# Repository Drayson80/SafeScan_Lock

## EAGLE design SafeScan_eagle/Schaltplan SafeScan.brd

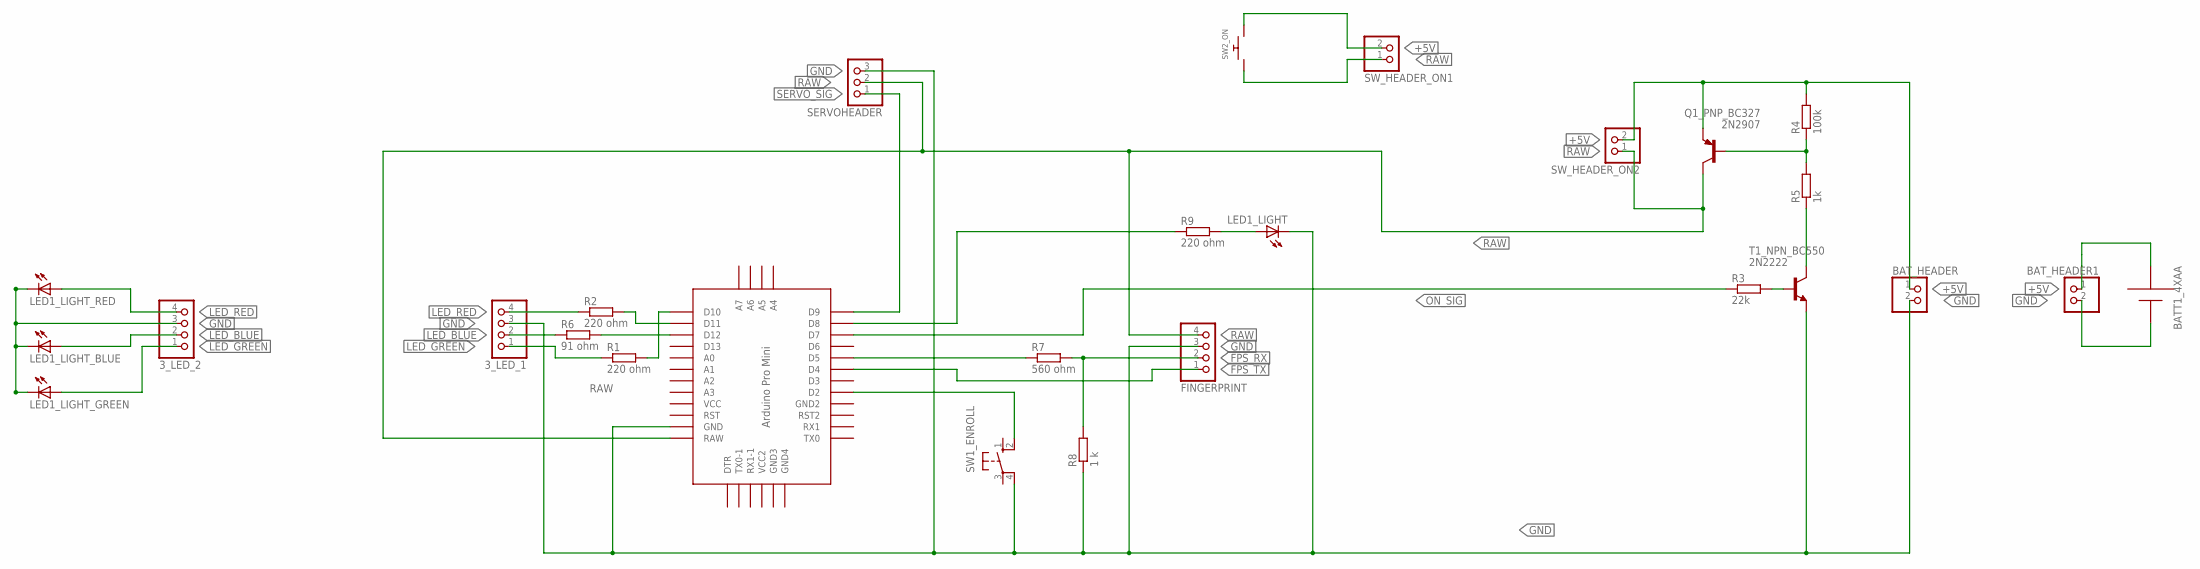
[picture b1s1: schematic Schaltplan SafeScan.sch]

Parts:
3_LED_1, 3_LED_2: PINHD-1X4; 1X04
ARDUINO_PRO_MINI_3.3: PRO-MINI
BATT1_4XAA: AAA; 12BH412
BAT_HEADER, BAT_HEADER1: PINHD-1X2; 1X02
FINGERPRINT: PINHD-1X4; 1X04
LED1_LIGHT, LED1_LIGHT_BLUE, LED1_LIGHT_GREEN, LED1_LIGHT_RED: LED5MM
Q1_PNP_BC327: 2N2907; TO92-EBC-OVAL
R1, R2, R9: 220 ohm; 0204/5
R3: 22k; 0204/5
R4: 100k; 0204/5
R5: 1k; 0204/5
R6: 91 ohm; 0204/5
R7: 560 ohm; 0207/15
R8: 1 k; 0204/5
SERVOHEADER: PINHD-1X3CB; 1X03-CLEANBIG
SW1_ENROLL: 10-XX; B3F-10XX
SW2_ON: SWITCH_PUSHBUTTONEVQ-PE; TACT_PANA-EVQ
SW_HEADER_ON1, SW_HEADER_ON2: PINHD-1X2; 1X02
T1_NPN_BC550: 2N2222; TO92-EBC-OVAL

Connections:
+5V: BATT1_4XAA.-, BAT_HEADER.1, BAT_HEADER1.1, Q1_PNP_BC327.E, R4.2, SW2_ON.P$2, SW_HEADER_ON1.2, SW_HEADER_ON2.2
FPS_RX: FINGERPRINT.2, R7.2, R8.2
FPS_TX: ARDUINO_PRO_MINI_3.3.D4, FINGERPRINT.1
GND: 3_LED_1.3, 3_LED_2.3, ARDUINO_PRO_MINI_3.3.GND, BATT1_4XAA.+, BAT_HEADER.2, BAT_HEADER1.2, FINGERPRINT.3, LED1_LIGHT.K (C), LED1_LIGHT_BLUE.K (C), LED1_LIGHT_GREEN.K (C), LED1_LIGHT_RED.K (C), R8.1, SERVOHEADER.3, SW1_ENROLL.4 (P1), T1_NPN_BC550.E
LED_BLUE: 3_LED_1.2, 3_LED_2.2, LED1_LIGHT_BLUE.A, R6.1
LED_GREEN: 3_LED_1.1, 3_LED_2.1, LED1_LIGHT_GREEN.A, R1.1
LED_RED: 3_LED_1.4, 3_LED_2.4, LED1_LIGHT_RED.A, R2.1
unnamed: ARDUINO_PRO_MINI_3.3.D5, R7.1
unnamed: R5.1, T1_NPN_BC550.C
unnamed: ARDUINO_PRO_MINI_3.3.D2, SW1_ENROLL.2 (S1)
unnamed: ARDUINO_PRO_MINI_3.3.D8, R9.1
unnamed: ARDUINO_PRO_MINI_3.3.D10, R1.2
unnamed: ARDUINO_PRO_MINI_3.3.D11, R2.2
unnamed: ARDUINO_PRO_MINI_3.3.D12, R6.2
unnamed: Q1_PNP_BC327.B, R4.1, R5.2
unnamed: LED1_LIGHT.A, R9.2
unnamed: R3.2, T1_NPN_BC550.B
ON_SIG: ARDUINO_PRO_MINI_3.3.D7, R3.1
RAW: ARDUINO_PRO_MINI_3.3.RAW, FINGERPRINT.4, Q1_PNP_BC327.C, SERVOHEADER.2, SW2_ON.P$1, SW_HEADER_ON1.1, SW_HEADER_ON2.1
SERVO_SIG: ARDUINO_PRO_MINI_3.3.D9, SERVOHEADER.1

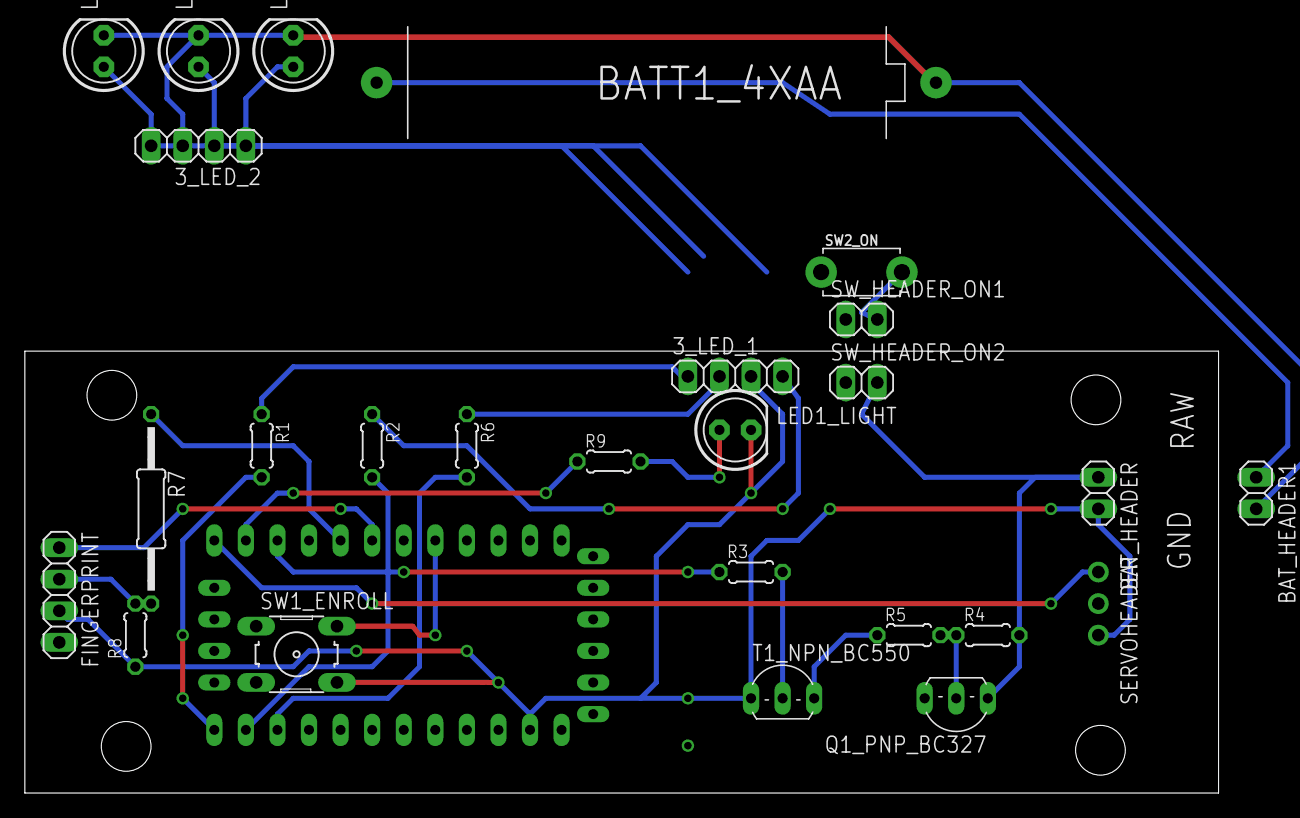
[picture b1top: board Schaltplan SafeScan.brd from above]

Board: 2 copper layers, 96.0 x 35.5 mm, 27 parts (0 on the bottom side), 20 nets.

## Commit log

2018-02-07 upload
    upload of status quo, first code iteration
2018-02-07 Improvements
    added self-holding power function, different power source, additional LED, restructured code...
2018-08-29 update infos
2018-09-06 Changes to make it work...
2018-09-07 rework...
2018-09-07 Add Selbsthaltung alternative
2018-09-10 Add mechanical Relais support for shutoff
2018-10-15 Add Schematics and Board Layout
2019-03-13 Add Info
    Speicherschutzbatterie
2019-03-13 Update/Generate Docu
    Dokumentation der Funktionen
